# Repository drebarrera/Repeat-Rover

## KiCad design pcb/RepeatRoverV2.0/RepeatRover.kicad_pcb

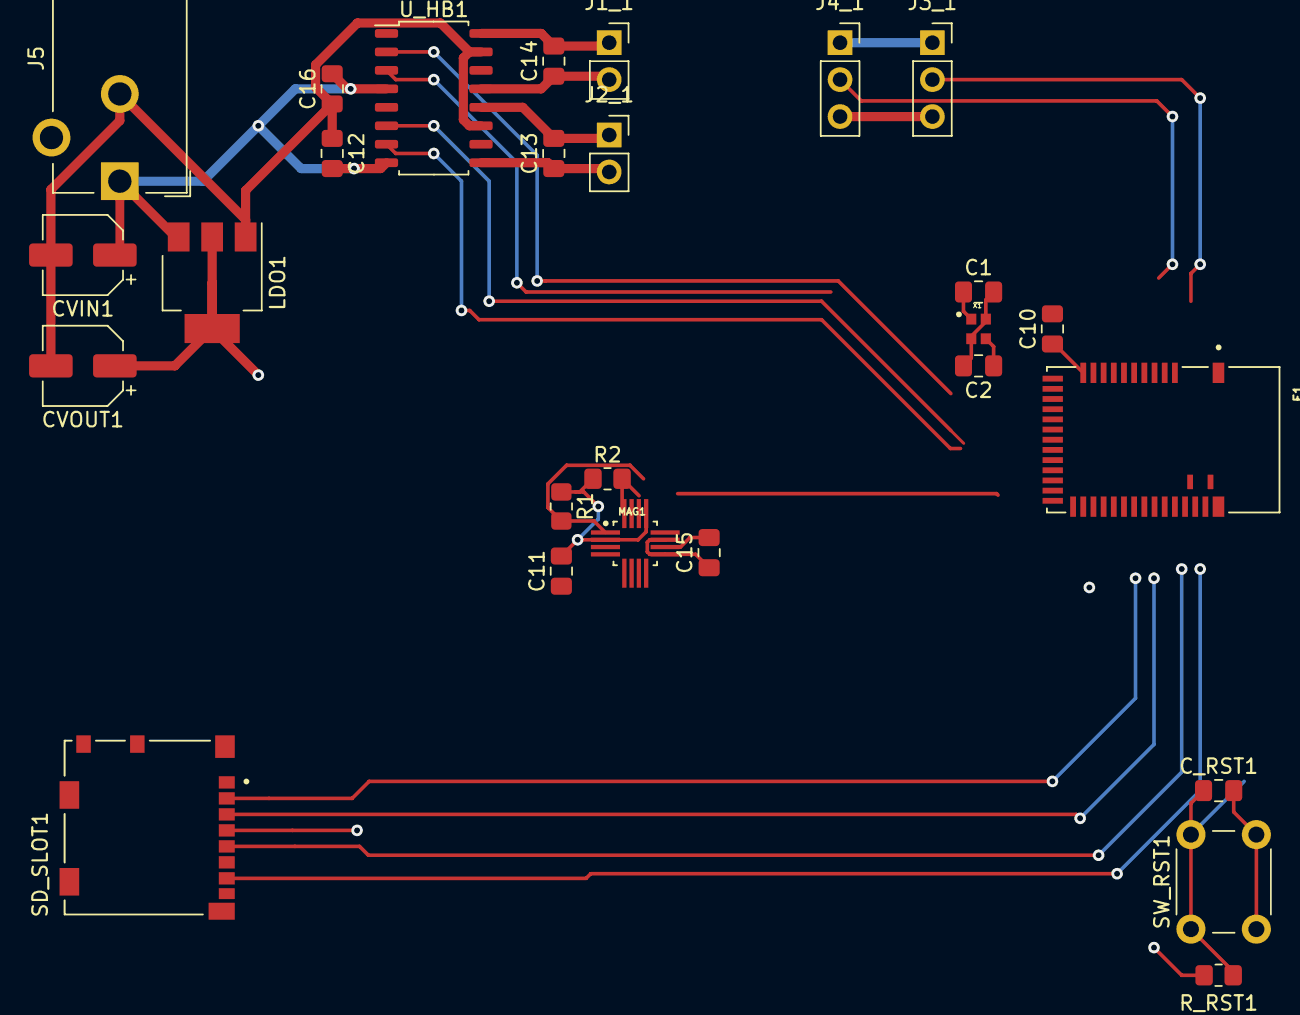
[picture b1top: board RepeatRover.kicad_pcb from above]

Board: 2 copper layers, 31 parts (0 on the bottom side), 23 nets.

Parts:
C1, C2: 12pF; C_0805_2012Metric_Pad1.18x1.45mm_HandSolder
C10, C11: 1uF; C_0805_2012Metric_Pad1.18x1.45mm_HandSolder
C12, C16: 100uF; C_0805_2012Metric_Pad1.18x1.45mm_HandSolder
C13, C14: .1uF; C_0805_2012Metric_Pad1.18x1.45mm_HandSolder
C15: 10uF; C_0805_2012Metric_Pad1.18x1.45mm_HandSolder
CVIN1: 10uF; CP_Elec_5x5.7
CVOUT1: 10uF; CP_Elec_5x5.7
C_RST1: 1uF; C_0805_2012Metric_Pad1.18x1.45mm_HandSolder
E1: MDBT42Q-512KV2; RAYTAC_MDBT42Q-512KV2
H1, H2, H3, H4: MountingHole; MountingHole_3.2mm_M3
J1_1, J2_1: Conn_01x02_Female; PinSocket_1x02_P2.54mm_Vertical
J3_1, J4_1: Conn_01x03_Female; PinSocket_1x03_P2.54mm_Vertical
J5: Barrel_Jack; BarrelJack_CUI_PJ-102AH_Horizontal
LDO1: NCP1117-3.3_SOT223; SOT-223-3_TabPin2
MAG1: MMC5983MA; PQFN50P300X300X100-16N
R1, R2: 2.7k; R_0805_2012Metric_Pad1.20x1.40mm_HandSolder
R_RST1: 10k; R_0805_2012Metric_Pad1.20x1.40mm_HandSolder
SD_SLOT1: 104031-0811; MOLEX_104031-0811
SW_RST1: _; SW_PUSH_6mm
U_HB1: YX1818BM; SOP-16_4.55x10.3mm_P1.27mm
X1: 32MHz; OSC_XRCGB32M000FXH2CR0

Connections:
+3V3: C10.1, C11.2, E1.11 (VDD), J3_1.1, J4_1.1, LDO1.2 (VO), MAG1.2 (VDD), MAG1.13 (VDDIO), R1.1, R2.1, R_RST1.1, SD_SLOT1.4 (VDD)
+6V: C12.2, C16.2, J5.1, LDO1.3 (VI), U_HB1.4 (VDD), U_HB1.8 (VDD)
/CS: E1.31 (P0.17), SD_SLOT1.2 (CD/DAT3)
/INA: E1.16 (P0.03), U_HB1.2 (INA)
/INB: E1.17 (P0.04), U_HB1.3 (INB)
/INC: E1.18 (P0.05), U_HB1.6 (INC)
/IND: E1.19 (P0.06), U_HB1.7 (IND)
/MISO: E1.34 (P0.20), SD_SLOT1.7 (DAT0)
/MOSI: E1.32 (P0.18), SD_SLOT1.3 (CMD)
/MSCL: C_RST1.1, E1.35 (P0.21/RESET), R_RST1.2, SW_RST1.1
/SCL: E1.22 (P0.09), MAG1.1 (SCL/SPI_SCK), R1.2
/SCLK: E1.33 (P0.19), SD_SLOT1.5 (CLK)
/SDA: E1.23 (P0.10), MAG1.16 (SDA/SPI_SDI), R2.2
/WSS1: E1.3 (P0.26), J3_1.2
/WSS2: E1.4 (P0.27), J4_1.2
/XC1: C1.1, E1.13 (P0.00/XL1), X1.1
/XC2: C2.1, E1.14 (P0.01/XL2), X1.3
GND: C1.2, C2.2, C10.2, C11.1, C12.1, C15.1, C16.1, CVIN1.2, CVOUT1.2, C_RST1.2, E1.1 (GND), E1.12 (GND), E1.24 (GND), E1.39 (GND), J3_1.3, J4_1.3, J5.2, LDO1.1 (GND), MAG1.9 (GND), MAG1.11 (GND), SD_SLOT1.6 (VSS), SD_SLOT1.G1 (GND), SD_SLOT1.G2 (GND), SD_SLOT1.G3 (GND), SD_SLOT1.G4 (GND), SW_RST1.2, U_HB1.11 (GND), U_HB1.15 (GND), X1.2, X1.4
unnamed: C13.1, J2_1.2, U_HB1.9 (OUTD)
unnamed: C13.2, J2_1.1, U_HB1.12 (OUTC)
unnamed: C14.1, J1_1.2, U_HB1.13 (OUTB)
unnamed: C14.2, J1_1.1, U_HB1.16 (OUTA)
unnamed: C15.2, MAG1.10 (CAP)

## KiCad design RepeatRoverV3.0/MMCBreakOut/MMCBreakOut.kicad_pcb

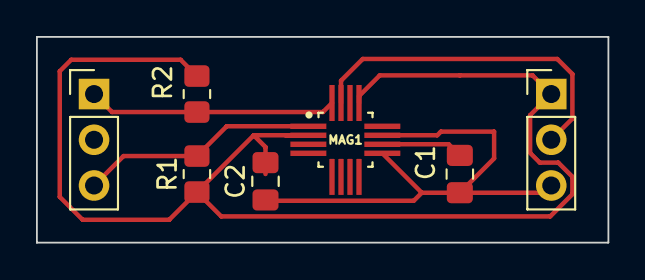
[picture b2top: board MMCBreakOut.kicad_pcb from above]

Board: 2 copper layers, 31.8 x 11.4 mm, 7 parts (0 on the bottom side), 6 nets.

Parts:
C1: 10u; C_0805_2012Metric_Pad1.18x1.45mm_HandSolder
C2: 1u; C_0805_2012Metric_Pad1.18x1.45mm_HandSolder
J1, J2: _; PinHeader_1x03_P2.54mm_Vertical
MAG1: MMC5983MA; PQFN50P300X300X100-16N
R1, R2: 2.7k; R_0805_2012Metric_Pad1.20x1.40mm_HandSolder

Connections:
+3V3: C2.2, J2.1, MAG1.2, MAG1.13, R1.1, R2.1
/INT: J2.2, MAG1.15
/SCL: J1.3, MAG1.1, R1.2
/SDA: J1.1, MAG1.16, R2.2
GND: C1.2, C2.1, J2.3, MAG1.9, MAG1.11
unnamed: C1.1, MAG1.10

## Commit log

2022-08-25 Added base directories
2022-08-25 commit fresh repository
2022-09-08 updates name
2022-09-08 Generates WebGen file for website
2022-09-14 Added nRF SDK
2022-09-14 added nrf sdk folder
2022-09-14 added Bluetooth files
2022-09-17 Update index page and about
2022-09-17 update index intro
2022-09-19 Website changes
2022-09-20 webgen update
2022-09-21 website compiled
2022-09-21 web updates
2022-09-23 added h-bridge
2022-09-23 updated mcu
2022-09-27 V3 W/ Partial PCB Design
    Added new H-Bridge Symbol, Mapped NRF required components, finished breakout board for MMC
2022-09-28 PCB with revisions from lecture
2022-09-28 new mcu footgprint
2022-09-29 On KiCad 6 with NRF Module Updates
2022-10-05 reorganizes github inventory
2022-10-06 added updated firmware
2022-10-06 readme firmware
2022-10-06 updated nrf52 sdk
2022-10-06 added ble stuff
2022-10-06 working project
2022-10-06 added readme
2022-10-06 added spi stuff
2022-10-20 Update main.c
    Change speed by changing value variable. For PWM speed control only.
2022-10-22 Creates gitignore
2022-11-05 uploads interface-app to repo
2022-11-11 Updating firmware
2022-11-11 added BLE firmware
2022-11-11 Update app
2022-11-13 Updates map with grid, obstacles, and bounds
2022-11-13 Updates map capabilities of app.
2022-11-13 App updates with button bar
2022-11-13 New Firmware project
2022-11-13 update firmware
2022-11-13 firmware updates
2022-11-14 App interface changes
2022-11-14 Update official project firmware
2022-11-14 Updates firmware folder name to firmware_sdk
2022-11-14 Updates internal firmware directory name to project_firmware
2022-11-16 app updates
2022-11-16 Adjusts firmware changes
2022-11-18 App adjustments
2022-11-24 updates app with turn delays
2022-11-28 added pwm
2022-11-30 updated pwm
2022-11-30 added sd card includes
2022-12-01 Added bluetooth functions
2022-12-02 BLE functions update
2022-12-03 added pwm includes
2022-12-04 App node.js updates
2022-12-04 updated sd and pwm
2022-12-04 Combine Includes
    Adds combine_includes python program to combine include directory lists.
2022-12-04 updated headers
2022-12-04 Mag Config
2022-12-04 Updates combine_configs
2022-12-04 sdk_config changes
2022-12-04 Debugs sd.c
2022-12-04 Bluetooth and main file modifications.
2022-12-04 latest BLE
2022-12-04 Firmware v.2
2022-12-06 Firmware updates to the peripherals.c and other components.
2022-12-06 Removes need for sd_open
2022-12-08 sd functions
2022-12-09 120822 2040 Firmware Update
2022-12-09 pushed fatfs folder
2022-12-10 Firmware Updates 121022
2022-12-11 changed period-1000L and duty cycle
2022-12-12 Firmware latest
2022-12-13 Firmware final
